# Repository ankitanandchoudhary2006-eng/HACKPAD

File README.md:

# HACKPAD

SO I make a 3x3 HACKPAD for myself . It is based on RP2040 and I tried it to make it compact as possible. It has a rotor Encoder as well . The PCB was designed on kicad and the CAD was designed on Fusion. It has diodes to prevent ghosting and LEDs as well. 

### Features
- Rp2040 Based
- Per switch LED
- Per switch diode for ghosting protection
- 3X3 Switch matrix design

 # Bill of Materials (BOM)

| Item | Price (USD) | Source |
|------|------------:|--------|
| PCB + Shipping  |  Already have| JLCPCB |
| Xiao RP2040  |  Already have | https://robocraze.com/products/seeed-studio-xiao-rp2040-development-board |
| Keycaps  |  Already have | https://meckeys.com/shop/accessories/keyboard-accessories/keycaps/blank/blank-dsa-keycaps-1u/ |
| Switches  |  Already have| https://neomacro.in/products/hmx-snowfall-tactile-switch |
| Hot-Swap Sockets | Already have| https://meckeys.com/shop/accessories/keyboard-accessories/key-switches/kailh-hot-swap-socket/ |
| Meckeys Shipping |  Already have | https://meckeys.com |
| Diodes  | Already have | https://www.indiamart.com/proddetail/1n4148-zener-diode-17117437048.html?srsltid=AY6E963bki0nwL2OinjlMEuWS0M70KFi09qZbGwOVNGWITkDFowKNj5A |
| Rotary Encoder | Already have | https://robu.in/product/hongyan-ec11h-7ce20p1zy15f7-rotary-encoder-with-push-button-switch-vertical-plug-in-5-pin/?gad_source=1&gad_campaignid=20363337560&gbraid=0AAAAADvLFWct9h45Mxed9zkPiGxGE94cn&gclid=Cj0KCQiA8aTYBhCvARIsAJFINlfZNuzLi7gixoSZKyuDWx-FxyBE6fwVGIXYczLEjFYsSskAcftmpAQaAnAbEALw_wcB|
| **Total** | **0.00** | |
  
# Schematics 

# PCB 

# CAD

# Built 

# Build Instruction 

First Solder the Diodes and the HotSwap then Solder the LEDS after that Solder the Xiao RP2040 Board and at the END solder the Rotor Encoder also before plugging it . Check if there is any mis-connection , shot or disconnection.

Working video link :- https://www.youtube.com/shorts/elLP0bpIYKg

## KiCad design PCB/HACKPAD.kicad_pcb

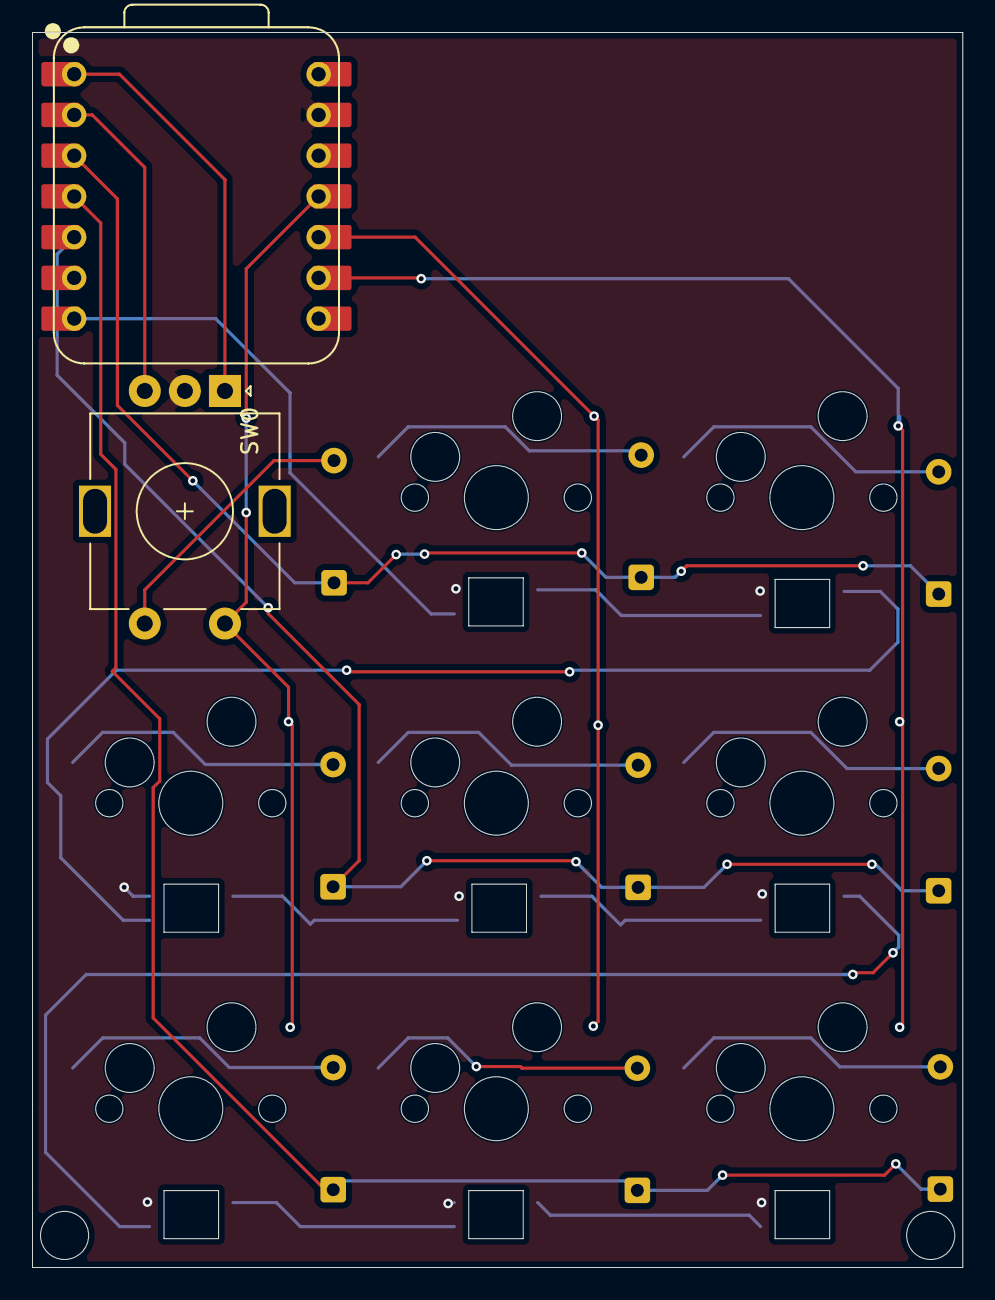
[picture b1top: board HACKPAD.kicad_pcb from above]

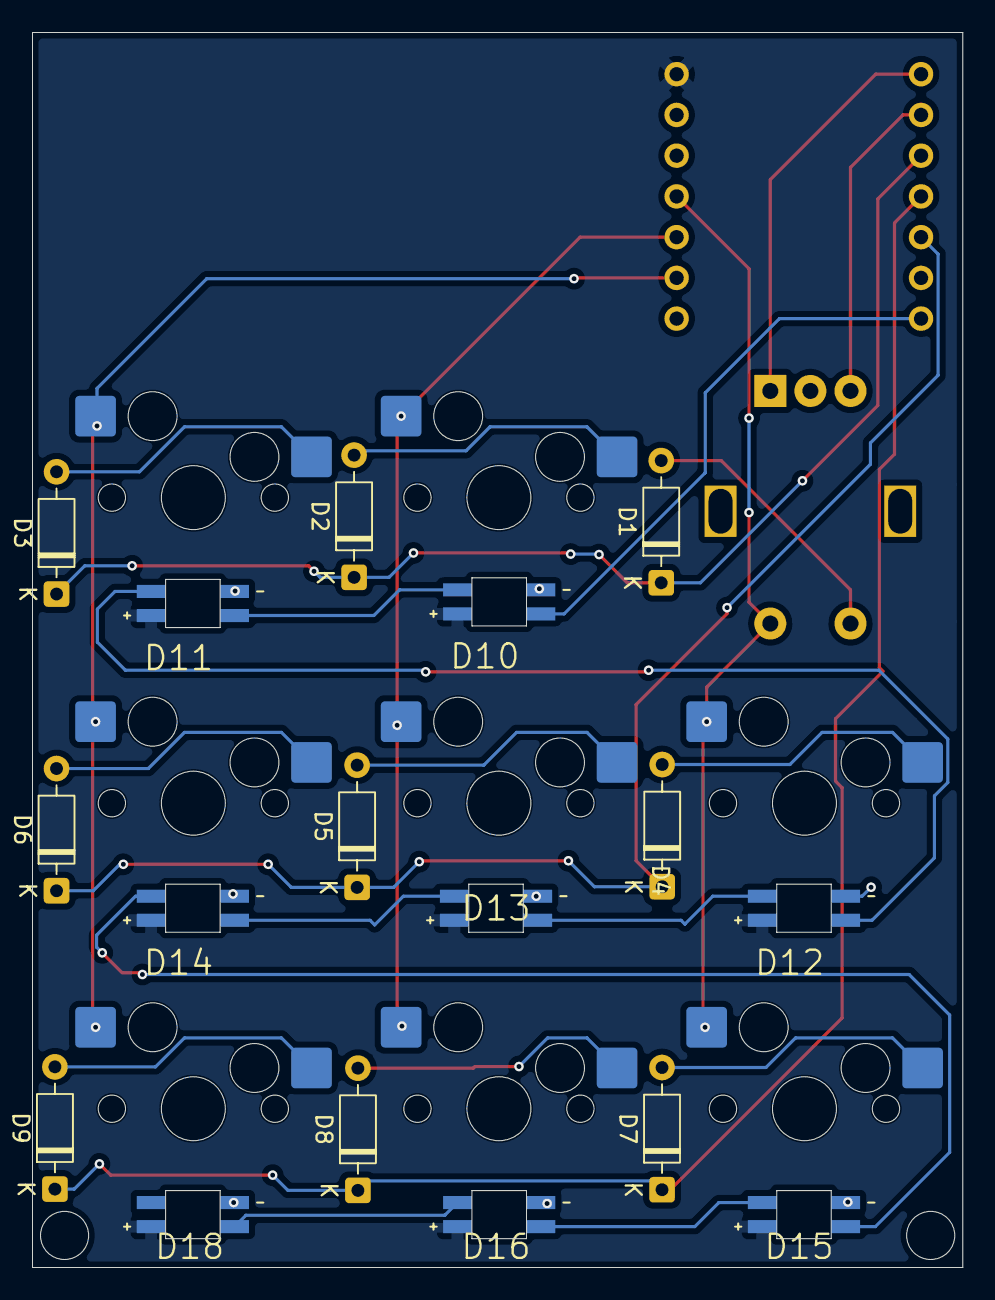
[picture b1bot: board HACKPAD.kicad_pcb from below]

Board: 2 copper layers, 58.0 x 77.0 mm, 27 parts (25 on the bottom side), 27 nets.

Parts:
D1, D2, D3, D4, D5, D6, D7, D8, D9: 1N4148; D_DO-35_SOD27_P7.62mm_Horizontal
D10, D11, D12, D13, D14, D15, D16, D18: SK6812-E; LED_SK6812-E
SW0: RotaryEncoder_Switch_MP; RotaryEncoder_Alps_EC11E-Switch_Vertical_H20mm
SW1, SW2, SW3, SW4, SW5, SW6, SW7, SW8: SW_Push; MX100H
U1: XIAO-RP2040-DIP

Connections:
+5V: D10.1 (VDD), D11.1 (VDD), D12.1 (VDD), D13.1 (VDD), D14.1 (VDD), D15.1 (VDD), D16.1 (VDD), D18.1 (VDD), U1.14 (VBUS)
C0: SW0.S2, SW3.1, SW6.1, U1.11 (GPIO3/MOSI)
C1: SW1.1, SW4.1, SW7.1, U1.10 (GPIO4/MISO)
C2: SW2.1, SW5.1, SW8.1, U1.9 (GPIO2/SCK)
GND: D10.3 (GND), D11.3 (GND), D12.3 (GND), D13.3 (GND), D14.3 (GND), D15.3 (GND), D16.3 (GND), D18.3 (GND), SW0.C, U1.13 (GND)
LED: D10.4 (DIN), U1.7 (GPIO0/TX)
unnamed: D1.2 (A), SW0.S1
unnamed: D2.2 (A), SW1.2
unnamed: D3.2 (A), SW2.2
unnamed: D4.2 (A), SW3.2
unnamed: D5.2 (A), SW4.2
unnamed: D6.2 (A), SW5.2
unnamed: D7.2 (A), SW6.2
unnamed: D8.2 (A), SW7.2
unnamed: D9.2 (A), SW8.2
unnamed: D10.2 (DOUT), D11.4 (DIN)
unnamed: D11.2 (DOUT), D12.4 (DIN)
unnamed: D12.2 (DOUT), D13.4 (DIN)
unnamed: D13.2 (DOUT), D14.4 (DIN)
unnamed: D14.2 (DOUT), D15.4 (DIN)
unnamed: D15.2 (DOUT), D16.4 (DIN)
unnamed: D16.2 (DOUT), D18.4 (DIN)
R0: D1.1 (K), D2.1 (K), D3.1 (K), U1.3 (GPIO28/ADC2/A2)
R1: D4.1 (K), D5.1 (K), D6.1 (K), U1.5 (GPIO6/SDA)
R2: D7.1 (K), D8.1 (K), D9.1 (K), U1.4 (GPIO29/ADC3/A3)
S1: SW0.A, U1.1 (GPIO26/ADC0/A0)
S2: SW0.B, U1.2 (GPIO27/ADC1/A1)
